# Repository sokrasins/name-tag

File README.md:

# MAKE Roanoke Name tag

A battery-powered, LED-lit "My name is" name tag for
MAKE Roanoke.

It is made of two stacked PCBs:

- **Back board:** holds all the electronics, including the battery, power
  switch, boost converter and 27 LEDs. This board provides 
  illumination to highlight the features on the front board.
- **Front board:** a plain faceplate with no parts. It has the "My name is:"
  silkscreen and a wrench graphic, and it covers the LED area of the back 
  board. The board lacks soldermask so that the wrench and the area with the 
  individual's name light up when the name tag is on.

The boards line up on four M3 mounting holes. They sandwich a 3D-printed
spacer between them and are held together with M3 nylon screws and nuts. The
spacer holds the boards apart so the LED light looks diffused through the
front board, and its walls stop the bright LED light from escaping out the
sides. A slot at the top of the back board is for a clip.

This project has been designed specifically to be built via reflow as part of a 
class.

Viewable links are here:
- [Schematic](https://github.com/sokrasins/nametag/blob/main/pcbs/nametag_back/nametag_back_schematic_rev4.pdf)
- [Back PCB](https://pcbview.io/?github=https%3A%2F%2Fgithub.com%2Fsokrasins%2Fnametag%2Fblob%2FHEAD%2Fpcbs%2Fnametag_back%2Fnametag_back.kicad_pcb)
- [Front PCB](https://pcbview.io/?github=https%3A%2F%2Fgithub.com%2Fsokrasins%2Fnametag%2Fblob%2FHEAD%2Fpcbs%2Fnametag_front%2Fnametag_front.kicad_pcb)
- [Assembly](https://htmlpreview.github.io/?https://raw.githubusercontent.com/sokrasins/nametag/refs/heads/main/pcbs/nametag_back/assembly/assembly_ibom.html)

## How it works

- **Power:** a single AA cell (Keystone 2460 holder) switched by an SPDT
  slide switch.
- **Boost converter:** a TI TPS613221A steps the cell up to a +3.3V rail.
- **LEDs:** 27× 1206 SMD LEDs (22 white, 5 green). Each one has its own
  current-limiting resistor to GND: 270 Ω for the white LEDs, 330 Ω for the
  green.
- **Brightness:** fixed. This revision (Rev 4) has no brightness control; the
  LEDs run at about 2.3–2.6 mA each whenever the switch is on. The board draws
  about 160–300 mA from the cell, which works out to roughly 8–10 hours on an
  alkaline AA or an eneloop.

See [pcbs/power_analysis.md](pcbs/power_analysis.md) for current draw and
battery life estimates.

## Boards

| | Back | Front |
| --- | --- | --- |
| Size | 100 × 78 mm | 100 × 53 mm |
| Layers / thickness | 2 / 1.6 mm | 2 / 0.8 mm |
| Components | All electronics | None (4× M3 holes) |

## Other parts needed

Besides the two PCBs and the parts in [pcbs/nametag_back/bom.csv](pcbs/nametag_back/bom.csv), each
name tag needs:

| Qty | Part | Notes |
| --- | --- | --- |
| 4 | M3 × 20 mm nylon screw | |
| 4 | M3 nylon nut | |
| 1 | 3D-printed spacer | [mech/nametag_spacer_v1.3mf](mech/nametag_spacer_v1.3mf) |
| 1 | Plastic name tag clip | Attaches through the slot at the top of the back board |

This exploded view shows how the boards, spacer, screws and nuts fit together:

<div align="center"></div>

## Printing the spacer

The spacer prints fine with your favorite standard settings. The
original was printed in black PLA, which helps block light from leaking out
the sides, but almost any filament should work.

## Adding your name

The front board leaves an open area for your name, and the LEDs behind it
light it up. How you fill it in is up to you. Some options:

- **Marker:** a Sharpie works, but it doesn't give much contrast against the
  lit board.
- **Letter stickers:** spell out your name with adhesive letters.
- **Cut vinyl:** cut your name or a design out of vinyl with a vinyl cutter.
- **Laser-cut design:** cut a design to sit over the name area.
- **Custom front PCB:** copy `pcbs/nametag_front/` and add your name as text,
  then order it in place of the default front board.

There are lots of creative possibilities, so have fun with it.

## Repository layout

| Path | Contents |
| --- | --- |
| `pcbs/nametag_back/` | Back board KiCad project (schematic and layout) |
| `pcbs/nametag_back/gerbs/` | Back board Gerbers and drill files |
| `pcbs/nametag_back/nametag_back_schematic_rev4.pdf` | Back board schematic PDF |
| `pcbs/nametag_front/` | Front board KiCad project (layout only, no schematic) |
| `pcbs/nametag_front/gerbs/` | Front board Gerbers and drill files |
| `pcbs/datasheets/` | Datasheets for the battery holder and boost converter |
| `pcbs/power_analysis.md` | Current draw and battery life estimates |
| `pcbs/nametag_back/assembly/assembly_ibom.html` | Interactive BOM for assembling the back board |
| `pcbs/nametag_back/assembly/assembly_guide.pdf` | Printable assembly guide, one step per component, two steps per page |
| `pcbs/nametag_back/assembly/assembly_guide_grayscale.pdf` | The same guide for black-and-white printers |
| `pcbs/nametag_back/bom.csv` | Bill of materials for the back board, with LCSC / Digi-Key part numbers |
| `mech/nametag_spacer_v1.3mf` | 3D-printable spacer |
| `docs/renders/` | Board and assembly renders used in this README |
| `docs/class_resources/` | Checklist for running a name tag class |
| `scripts/` | Scripts that generate the renders, schematic PDF and assembly docs ([usage](scripts/README.md)) |

## Notes

- **No useful battery cutoff:** once running, the boost converter (TPS613221A)
  keeps drawing power until the cell falls to about 0.4 V, where its
  undervoltage lockout finally trips. That is far below a safe end-of-discharge
  voltage (~0.9–1.0 V), so the badge will happily over-discharge the battery.
  Don't leave it on until it dies: switch it off when it starts to blink or
  drop out, and replace an alkaline cell or recharge an eneloop promptly. Deep
  discharge shortens NiMH cell life and makes alkaline cells more likely to
  leak. See [pcbs/power_analysis.md](pcbs/power_analysis.md).

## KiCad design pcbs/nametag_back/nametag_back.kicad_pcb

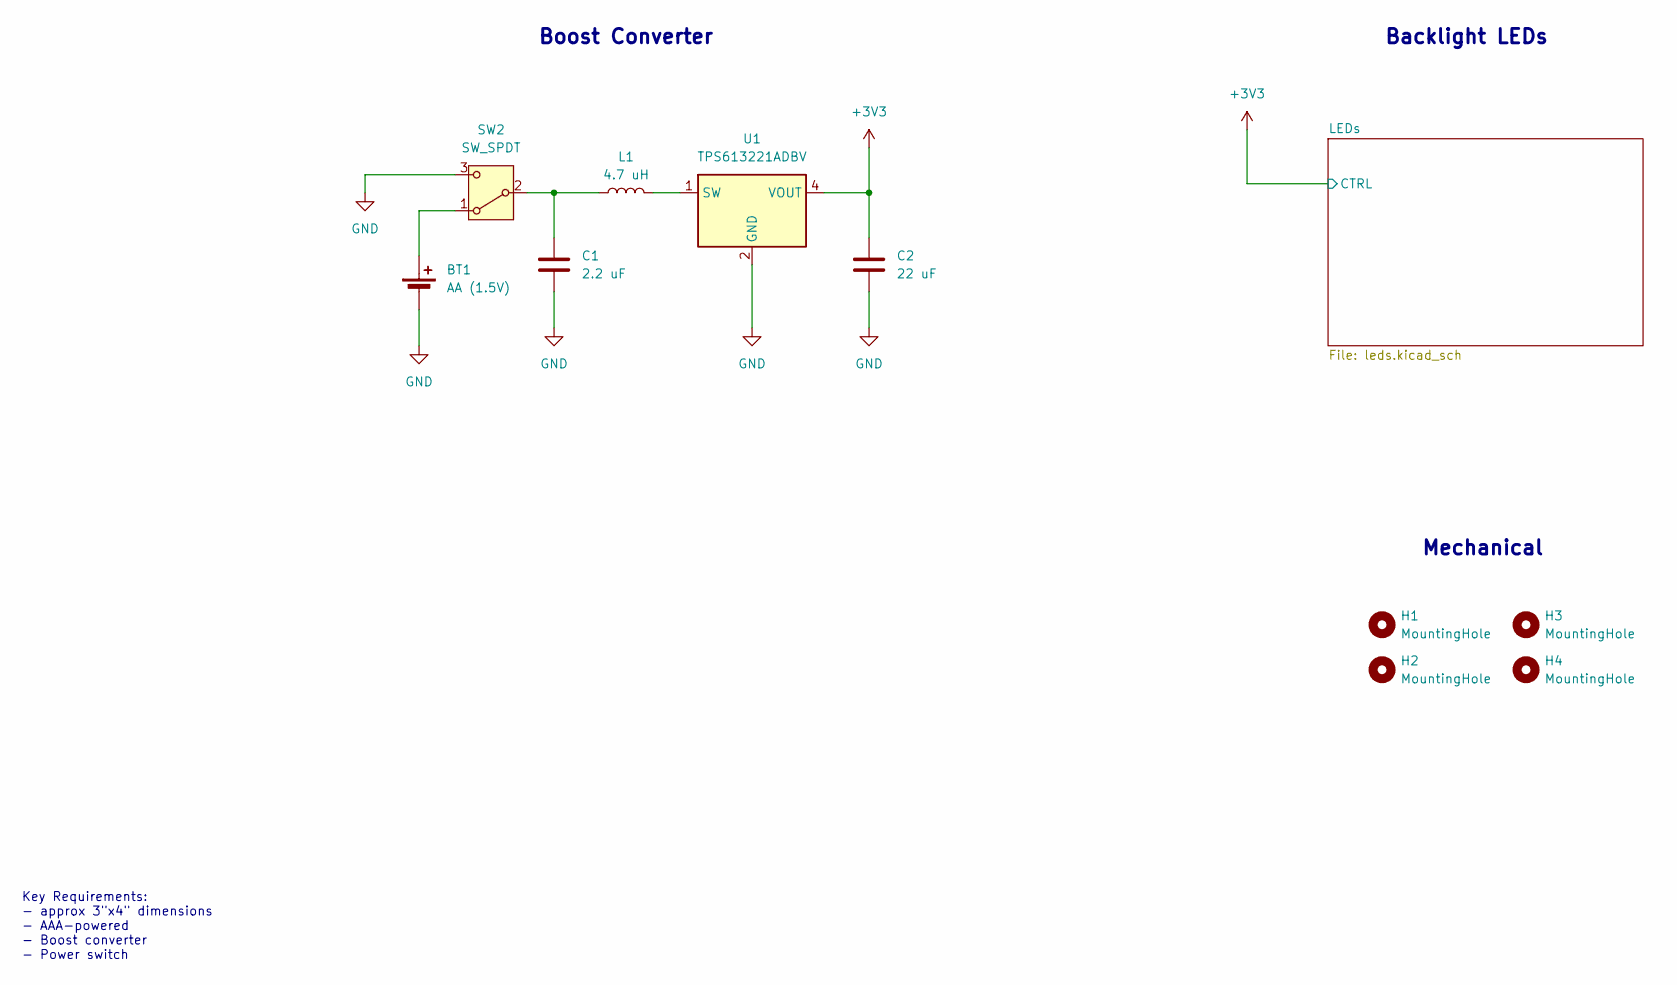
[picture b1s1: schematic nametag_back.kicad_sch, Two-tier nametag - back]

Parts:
BT1: AA (1.5V); BatteryHolder_Keystone_2460_1xAA
C1: 2.2 uF; C_0805_2012Metric
C2: 22 uF; C_0805_2012Metric
H1, H2, H3, H4: MountingHole; MountingHole_3.2mm_M3
L1: 4.7 uH; L_1008_2520Metric
SW2: SW_SPDT; SW_SPDT_PCM12
U1: TPS613221ADBV; SOT-23-5

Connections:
+3V3: C2.1, U1.4 (VOUT); also elsewhere on the board
GND: BT1.2 (-), C1.2, C2.2, SW2.3 (C), U1.2 (GND); also elsewhere on the board
unnamed: BT1.1 (+), SW2.1 (A)
unnamed: C1.1, L1.1, SW2.2 (B)
unnamed: L1.2, U1.1 (SW)

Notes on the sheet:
Backlight LEDs
Boost Converter
Key Requirements: - approx 3"x4" dimensions - AAA-powered - Boost converter - Power switch
Mechanical

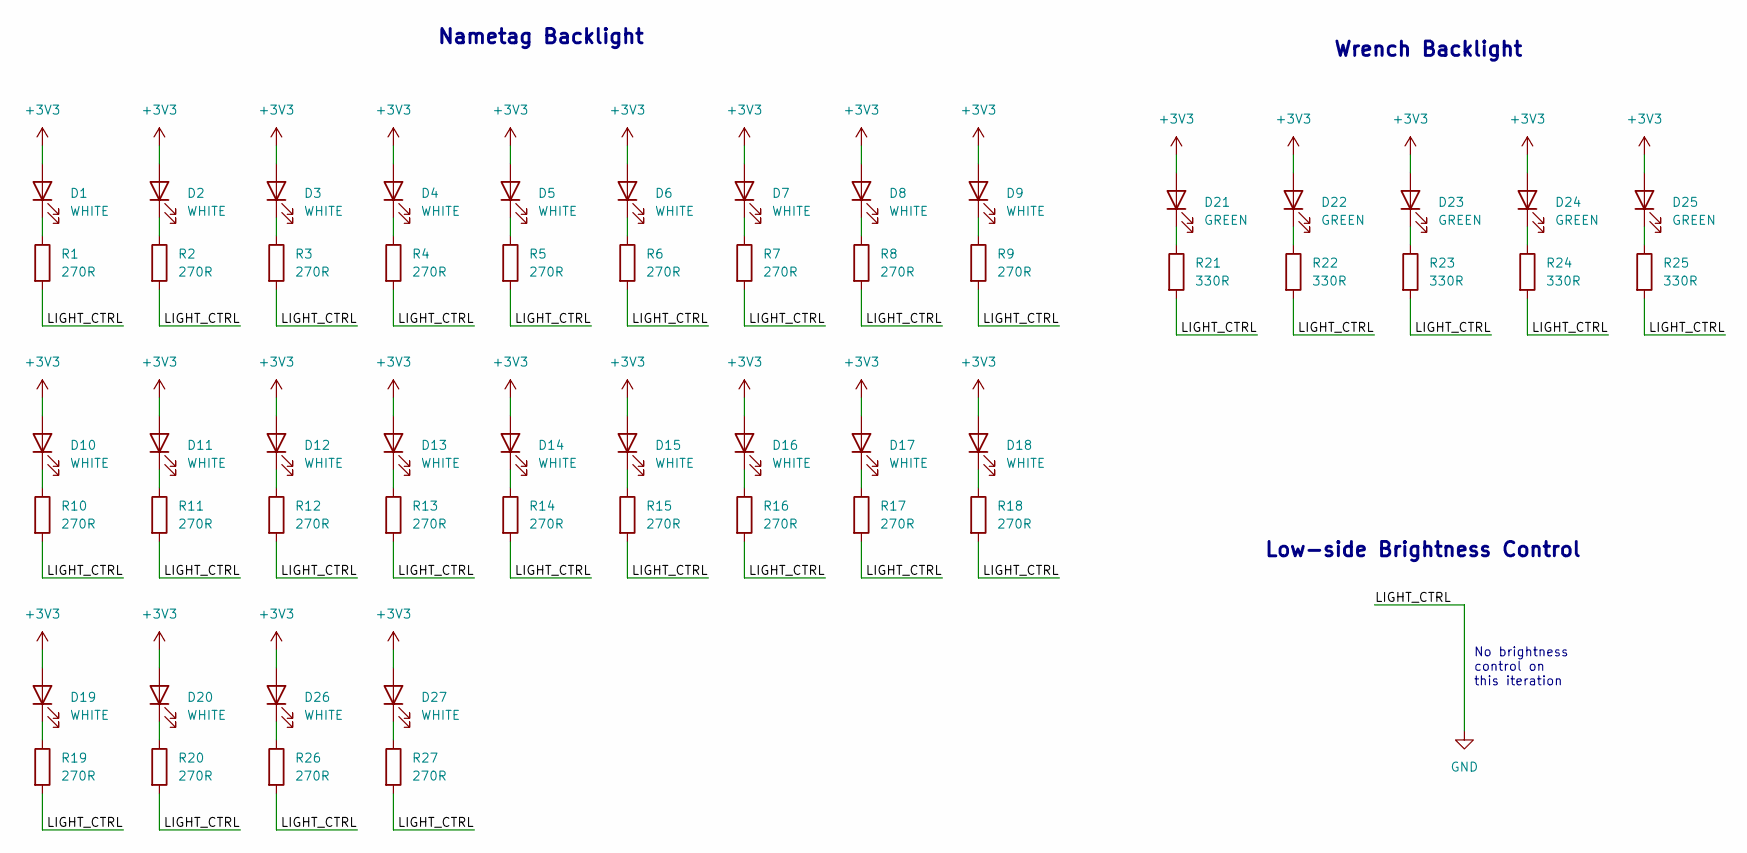
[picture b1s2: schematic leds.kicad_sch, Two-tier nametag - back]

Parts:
D1, D2, D3, D4, D5, D6, D7, D8, D9, D10, D11, D12, D13, D14, D15, D16, D17, D18, D19, D20, D26, D27: WHITE; LED_1206_3216Metric
D21, D22, D23, D24, D25: GREEN; LED_1206_3216Metric
R1, R2, R3, R4, R5, R6, R7, R8, R9, R10, R11, R12, R13, R14, R15, R16, R17, R18, R19, R20, R26, R27: 270R; R_0805_2012Metric
R21, R22, R23, R24, R25: 330R; R_0805_2012Metric

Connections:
+3V3: D1.2 (A), D2.2 (A), D3.2 (A), D4.2 (A), D5.2 (A), D6.2 (A), D7.2 (A), D8.2 (A), D9.2 (A), D10.2 (A), D11.2 (A), D12.2 (A), D13.2 (A), D14.2 (A), D15.2 (A), D16.2 (A), D17.2 (A), D18.2 (A), D19.2 (A), D20.2 (A), D21.2 (A), D22.2 (A), D23.2 (A), D24.2 (A), D25.2 (A), D26.2 (A), D27.2 (A); also elsewhere on the board
GND: R1.2, R2.2, R3.2, R4.2, R5.2, R6.2, R7.2, R8.2, R9.2, R10.2, R11.2, R12.2, R13.2, R14.2, R15.2, R16.2, R17.2, R18.2, R19.2, R20.2, R21.2, R22.2, R23.2, R24.2, R25.2, R26.2, R27.2; also elsewhere on the board
unnamed: D1.1 (K), R1.1
unnamed: D2.1 (K), R2.1
unnamed: D3.1 (K), R3.1
unnamed: D4.1 (K), R4.1
unnamed: D5.1 (K), R5.1
unnamed: D6.1 (K), R6.1
unnamed: D7.1 (K), R7.1
unnamed: D8.1 (K), R8.1
unnamed: D9.1 (K), R9.1
unnamed: D10.1 (K), R10.1
unnamed: D11.1 (K), R11.1
unnamed: D12.1 (K), R12.1
unnamed: D13.1 (K), R13.1
unnamed: D14.1 (K), R14.1
unnamed: D15.1 (K), R15.1
unnamed: D16.1 (K), R16.1
unnamed: D17.1 (K), R17.1
unnamed: D18.1 (K), R18.1
unnamed: D19.1 (K), R19.1
unnamed: D20.1 (K), R20.1
unnamed: D21.1 (K), R21.1
unnamed: D22.1 (K), R22.1
unnamed: D23.1 (K), R23.1
unnamed: D24.1 (K), R24.1
unnamed: D25.1 (K), R25.1
unnamed: D26.1 (K), R26.1
unnamed: D27.1 (K), R27.1

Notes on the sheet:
Nametag Backlight
No brightness control on this iteration
Wrench Backlight
Low-side Brightness Control

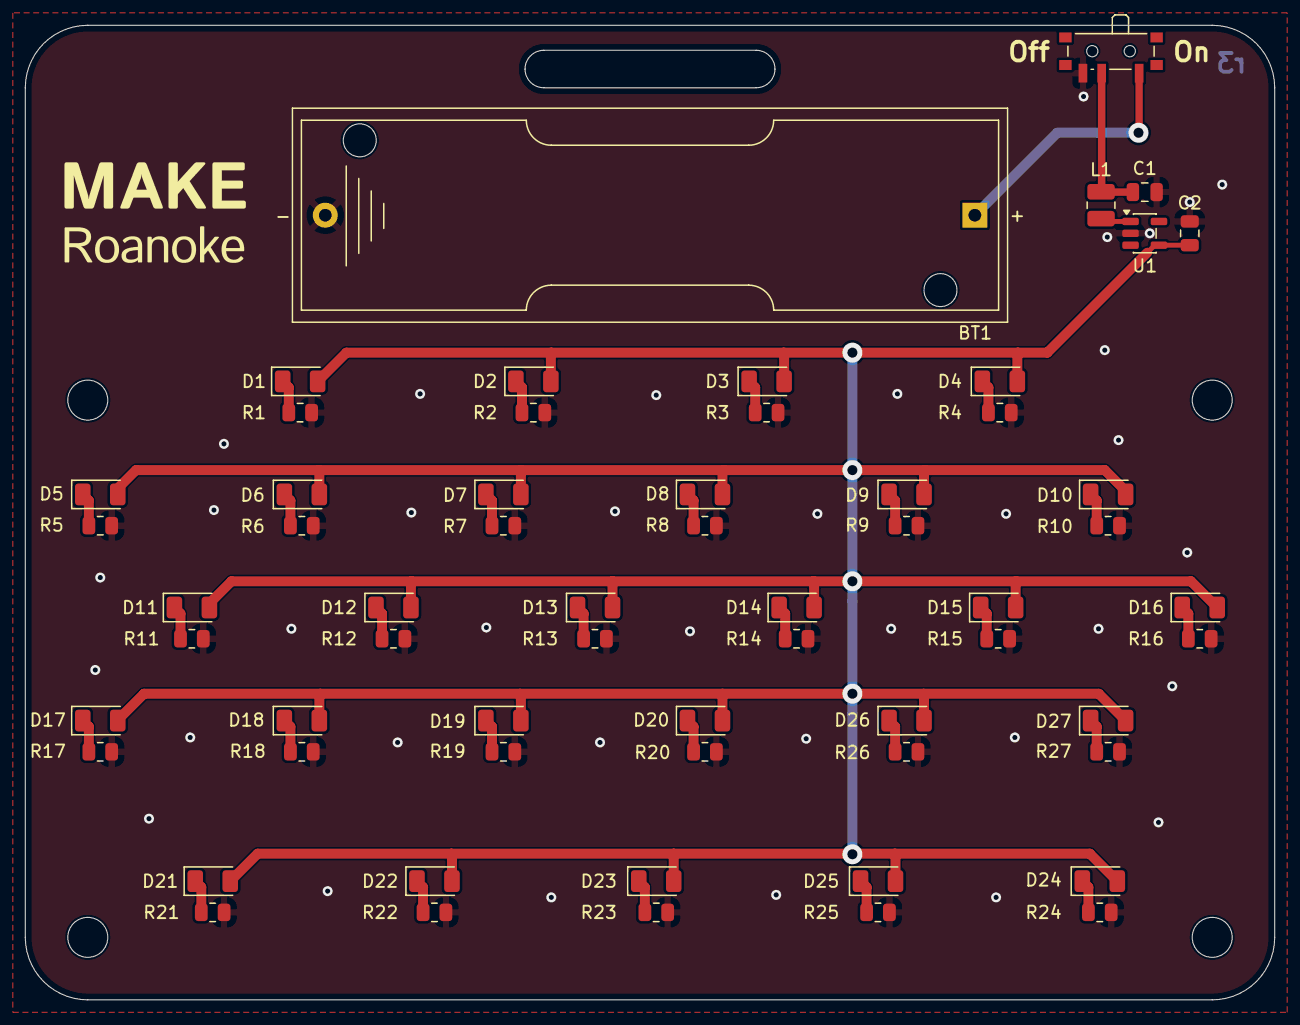
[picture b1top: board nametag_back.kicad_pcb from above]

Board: 2 copper layers, 100.0 x 78.0 mm, 64 parts (0 on the bottom side), 32 nets.
